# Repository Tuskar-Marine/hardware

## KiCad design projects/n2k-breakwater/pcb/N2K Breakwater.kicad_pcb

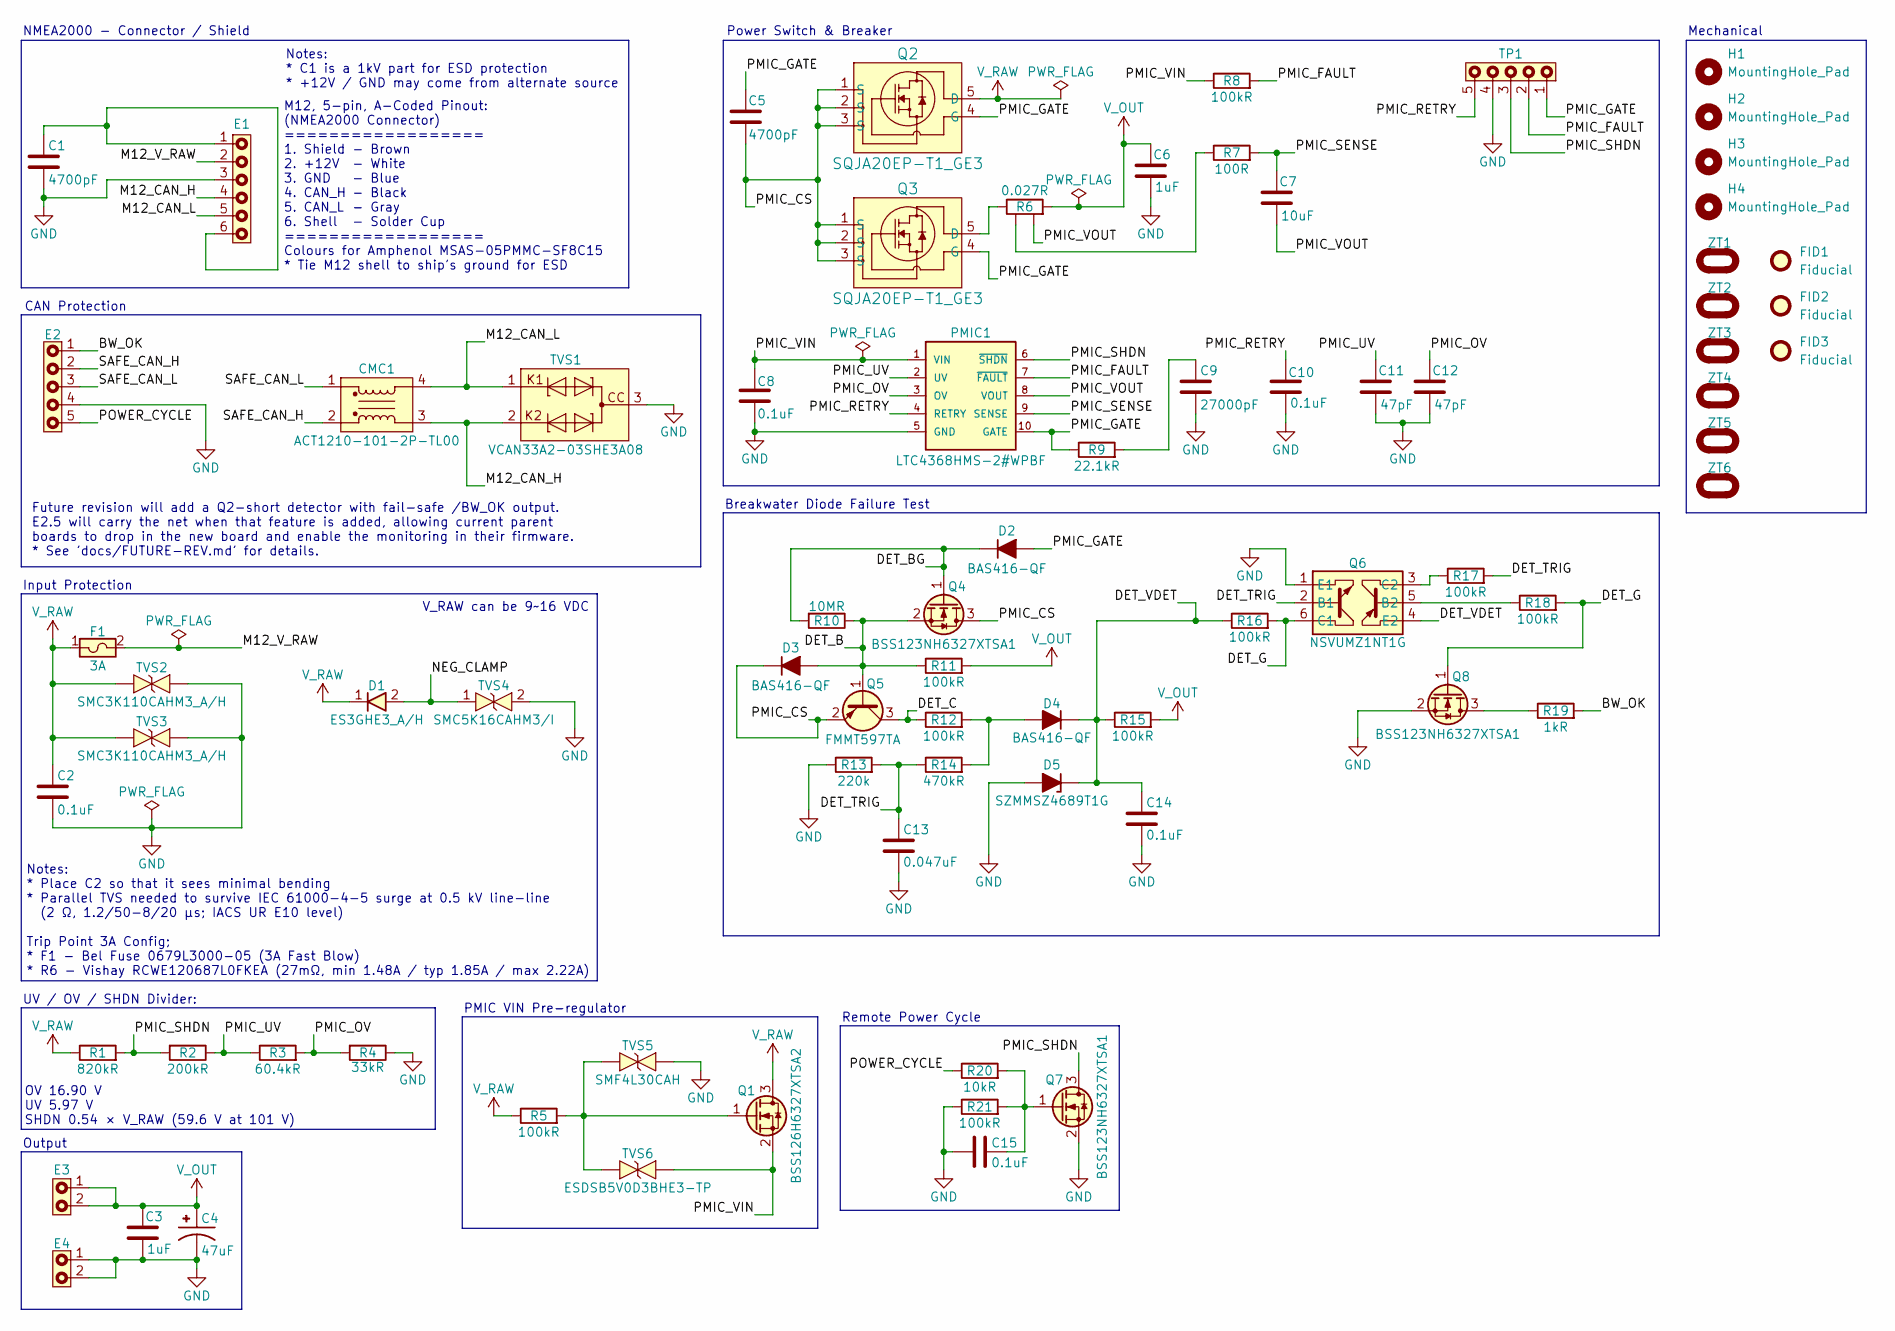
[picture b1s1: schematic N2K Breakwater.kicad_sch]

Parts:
C1, C5: 4700pF; Murata GCJ31BR73A; Part Murata GCJ31BR73A472KXJ1L
C2: 0.1uF; TDK CGA5; Part TDK CGA5L3X7R2E104K160AE
C3, C6: 1uF; Kyocera AVX 0805; Part Kyocera 08051C105K4Z2A
C4: 47uF; Nichicon PCM; Part Nichicon PCM1V470MCL1GS
C7: 10uF; TDK CGA5; Part TDK CGA5L1X7R1H106K160AE
C8, C10, C14, C15: 0.1uF; Kyocera AVX 0805; Part Kyocera 08051C104K4Z2A
C9: 27000pF; Murata GCM0805; Part Murata GCM21B5C2A273JE02K
C11, C12: 47pF; Kemet C0805X; Part Kemet C0805X470J5GACAUTO
C13: 0.047uF; Murata GCJ 0805; Part Murata GCJ21BR72A473KA01L
CMC1: ACT1210-101-2P-TL00; TDK ACT12101012PTL00; Part TDK ACT1210-101-2P-TL00
D1: ES3GHE3_A/H; Vishay ES3G; Part Vishay ES3GHE3_A/H
D2, D3, D4: BAS416-QF; Nexperia BAS416-QF; Part Nexperia BAS416-QF
D5: SZMMSZ4689T1G; Onsemi SZMMSZ4689; Part Onsemi SZMMSZ4689T1G
E1: WireSolderPoint - 1x06 - 2.5mm pitch x 1.0mm diameter; Part n/a
E2: WireSolderPoint - 1x05 - 2.5mm pitch x 1.0mm diameter; Part n/a
E3, E4: WireSolderPoint - 1x02 - 2.5mm pitch x 1.0mm diameter; Part n/a
F1: 3A; Bel Fuse 0679L; Part Bel Fuse 0679L3000-05
FID1, FID2, FID3: Fiducial; Fiducial_1mm_Mask2mm
H1, H2, H3, H4: MountingHole_Pad; MountingHole_5mm_M4_with_Keepout
PMIC1: LTC4368HMS-2#WPBF; ADI LTC4368; Part ADI LTC4368HMS-2#WPBF
Q1: BSS126H6327XTSA2; Infineon BSS126; Part Infineon BSS126H6327XTSA2
Q2, Q3: SQJA20EP-T1_GE3; Vishay SQJA20; Part Vishay SQJA20EP-T1_GE3
Q4, Q7, Q8: BSS123NH6327XTSA1; Infineon BSS123; Part Infineon BSS123NH6327XTSA1
Q5: FMMT597TA; Diodes Inc FMMT597TA; Part Diodes Inc FMMT597TA
Q6: NSVUMZ1NT1G; Onsemi NSVUMZ1; Part Onsemi NSVUMZ1NT1G
R1: 820kR; Panasonic ERA-6K 0805; Part Panasonic ERA-6KEB8203V
R2: 200kR; Stackpole RMCA0603; Part Stackpole RMCA0603FT200K-HP
R3: 60.4kR; Vishay RCA e3 0805; Part Vishay RCA080560K4FKEA
R4: 33kR; Stackpole RMCA0603; Part Stackpole RMCA0603FT33K0-HP
R5, R8, R11, R12, R15, R16, R17, R18, R21: 100kR; Stackpole RMCA0805; Part Stackpole RMCA0805FT100K-HP
R6: 0.027R; Vishay RCWE 1206 4-wire Kelvin; Part Vishay RCWE120627L0FMEA
R7: 100R; Stackpole RMCA0805; Part Stackpole RMCA0805FT100R-HP
R9: 22.1kR; Stackpole RNCP0805; Part Stackpole RNCP0805FTD22K1
R10: 10MR; Stackpole RMCA0603; Part Stackpole RMCA0603FT10M0-HP
R13: 220k; Panasonic ERJ-PC6; Part Panasonic ERJ-PC6D2203V
R14: 470kR; Wurth WRIS-RSKS; Part Wurth 560112120009
R19: 1kR; Stackpole RNCP0805; Part Stackpole RNCP0805FTD1K00
R20: 10kR; Stackpole RNCP0805; Part Stackpole RNCP0805FTD10K0
TP1: WireSolderPoint - 1x05 - 2.5mm pitch x 1.0mm diameter; Part n/a
TVS1: VCAN33A2-03SHE3A08; Vishay VCAN33A2-03S; Part Vishay VCAN33A2-03SHE3A08
TVS2, TVS3: SMC3K110CAHM3_A/H; Vishay SMC3K110; Part Vishay SMC3K110CAHM3_A/H
TVS4: SMC5K16CAHM3/I; Vishay SMC5K16CA; Part Vishay SMC5K16CAHM3/I
TVS5: SMF4L30CAH; TSC SMF4L30CAH; Part TSC SMF4L30CAH
TVS6: ESDSB5V0D3BHE3-TP; MCC ESDSB5V0D3; Part MCC ESDSB5V0D3BHE3-TP
ZT1, ZT2, ZT3, ZT4, ZT5, ZT6: Tuskar Ziptie Slot 4.5x2mm

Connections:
/BW_OK: E2.1, R19.2
/DET_B: D3.2 (A), Q4.2 (S), Q5.1 (B), R10.2, R11.1
/DET_BG: D2.1 (K), Q4.1 (G), R10.1
/DET_C: Q5.3 (C), R12.1
/DET_G: Q6.6 (C1), Q8.1 (G), R16.2, R18.2
/DET_TRIG: C13.1, Q6.2 (B1), R13.2, R14.1, R17.2
/DET_VDET: C14.1, D4.1 (K), D5.1 (K), Q6.4 (E2), R15.1, R16.1
/M12_CAN_H: CMC1.3 (O2), E1.4, TVS1.2
/M12_CAN_L: CMC1.4 (O1), E1.5, TVS1.1
/M12_V_RAW: E1.2, F1.2
/NEG_CLAMP: D1.2 (A), TVS4.1
/PMIC_CS: C5.1, D3.1 (K), Q2.1 (S), Q2.2 (S), Q2.3 (S), Q3.1 (S), Q3.2 (S), Q3.3 (S), Q4.3 (D), Q5.2 (E)
/PMIC_FAULT: PMIC1.7 (~FAULT), R8.2, TP1.2
/PMIC_GATE: C5.2, D2.2 (A), PMIC1.10 (GATE), Q2.4 (G), Q3.4 (G), R9.1, TP1.1
/PMIC_OV: C12.1, PMIC1.3 (OV), R3.2, R4.1
/PMIC_RETRY: C10.2, PMIC1.4 (RETRY), TP1.5
/PMIC_SENSE: C7.2, PMIC1.9 (SENSE), R7.2
/PMIC_SHDN: PMIC1.6 (~SHDN), Q7.3 (D), R1.2, R2.1, TP1.3
/PMIC_UV: C11.1, PMIC1.2 (UV), R2.2, R3.1
/PMIC_VIN: C8.1, PMIC1.1 (VIN), Q1.2 (S), R8.1, TVS6.2
/PMIC_VOUT: C7.1, PMIC1.8 (VOUT), R6.3
/POWER_CYCLE: E2.5, R20.1
/SAFE_CAN_H: CMC1.2 (I2), E2.2
/SAFE_CAN_L: CMC1.1 (I1), E2.3
GND: C1.1, C2.2, C3.2, C4.2, C6.2, C8.2, C9.2, C10.1, C11.2, C12.2, C13.2, C14.2, C15.1, D5.2 (A), E1.3, E2.4, E4.1, E4.2, PMIC1.5 (GND), Q6.1 (E1), Q7.2 (S), Q8.2 (S), R4.2, R13.1, R21.1, TP1.4, TVS1.3, TVS2.2, TVS3.2, TVS4.2, TVS5.2
unnamed: C1.2, E1.1, E1.6
unnamed: C9.1, R9.2
unnamed: D4.2 (A), R12.2, R14.2
unnamed: Q1.1 (G), R5.2, TVS5.1, TVS6.1
unnamed: Q3.5 (D), R6.2
unnamed: Q6.5 (B2), R18.1
unnamed: Q6.3 (C2), R17.1
unnamed: C15.2, Q7.1 (G), R20.2, R21.2
unnamed: Q8.3 (D), R19.1
unnamed: R6.4, R7.1
V_OUT: C3.1, C4.1, C6.1, E3.1, E3.2, R6.1, R11.2, R15.2
V_RAW: C2.1, D1.1 (K), F1.1, Q1.3 (D), Q2.5 (D), R1.1, R5.1, TVS2.1, TVS3.1

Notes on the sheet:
Remote Power Cycle
CAN Protection
V_RAW can be 9~16 VDC
PMIC VIN Pre-regulator
Output
Notes: * C1 is a 1kV part for ESD protection * +12V / GND may come from alternate source
M12, 5-pin, A-Coded Pinout: (NMEA2000 Connector) ================== 1. Shield 2. +12V 3. GND 4. CAN_H 5. CAN_L 6. Shell ================== Colours for Amphenol MSAS-05PMMC-SF8C15 * Tie M12 shell to ship's ground for ESD
Future revision will add a Q2-short detector with fail-safe /BW_OK output. E2.5 will carry the net when that feature is added, allowing current parent boards to drop in the new board and enable the monitoring in their firmware. * See 'docs/FUTURE-REV.md' for details.
Input Protection
Power Switch & Breaker
UV / OV / SHDN Divider:
Notes: * Place C2 so that it sees minimal bending * Parallel TVS needed to survive IEC 61000-4-5 surge at 0.5 kV line-line (2 Ω, 1.2/50-8/20 µs; IACS UR E10 level) Trip Point 3A Config; * F1 - Bel Fuse 0679L3000-05 (3A Fast Blow) * R6 - Vishay RCWE120687L0FKEA (27mΩ, min 1.48A / typ 1.85A / max 2.2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
NMEA2000 - Connector / Shield
Breakwater Diode Failure Test
Mechanical
OV 16.90 V UV 5.97 V SHDN 0.54 × V_RAW (59.6 V at 101 V)
- Brown - White - Blue - Black - Gray - Solder Cup

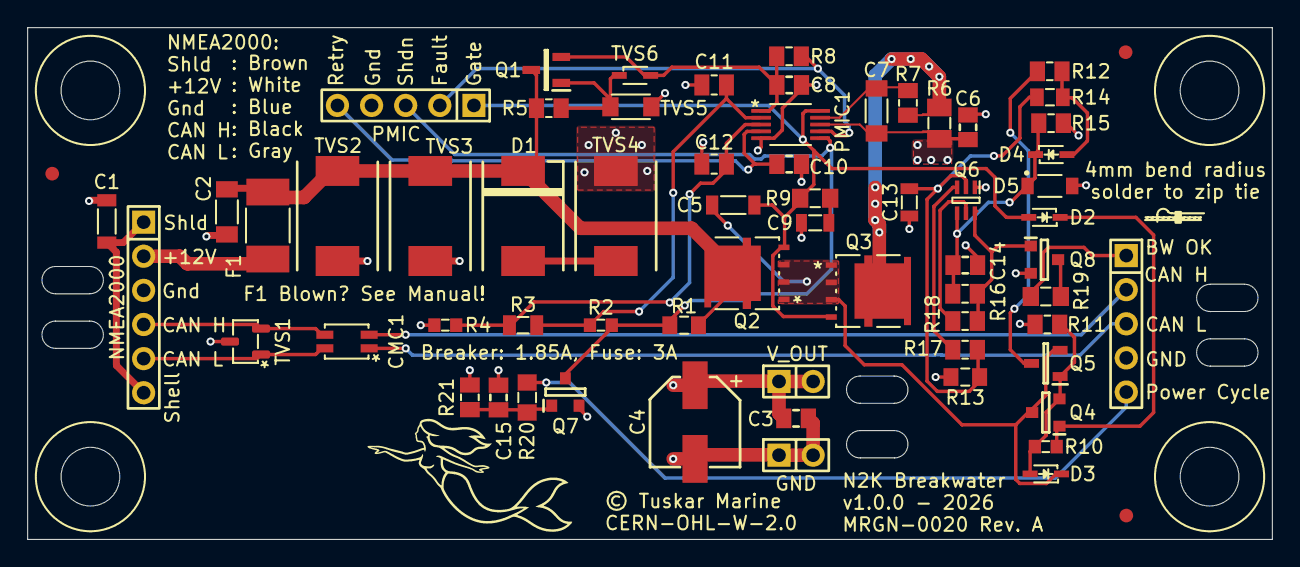
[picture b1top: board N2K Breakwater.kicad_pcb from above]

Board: 4 copper layers, 91.2 x 37.5 mm, 76 parts (0 on the bottom side), 37 nets.

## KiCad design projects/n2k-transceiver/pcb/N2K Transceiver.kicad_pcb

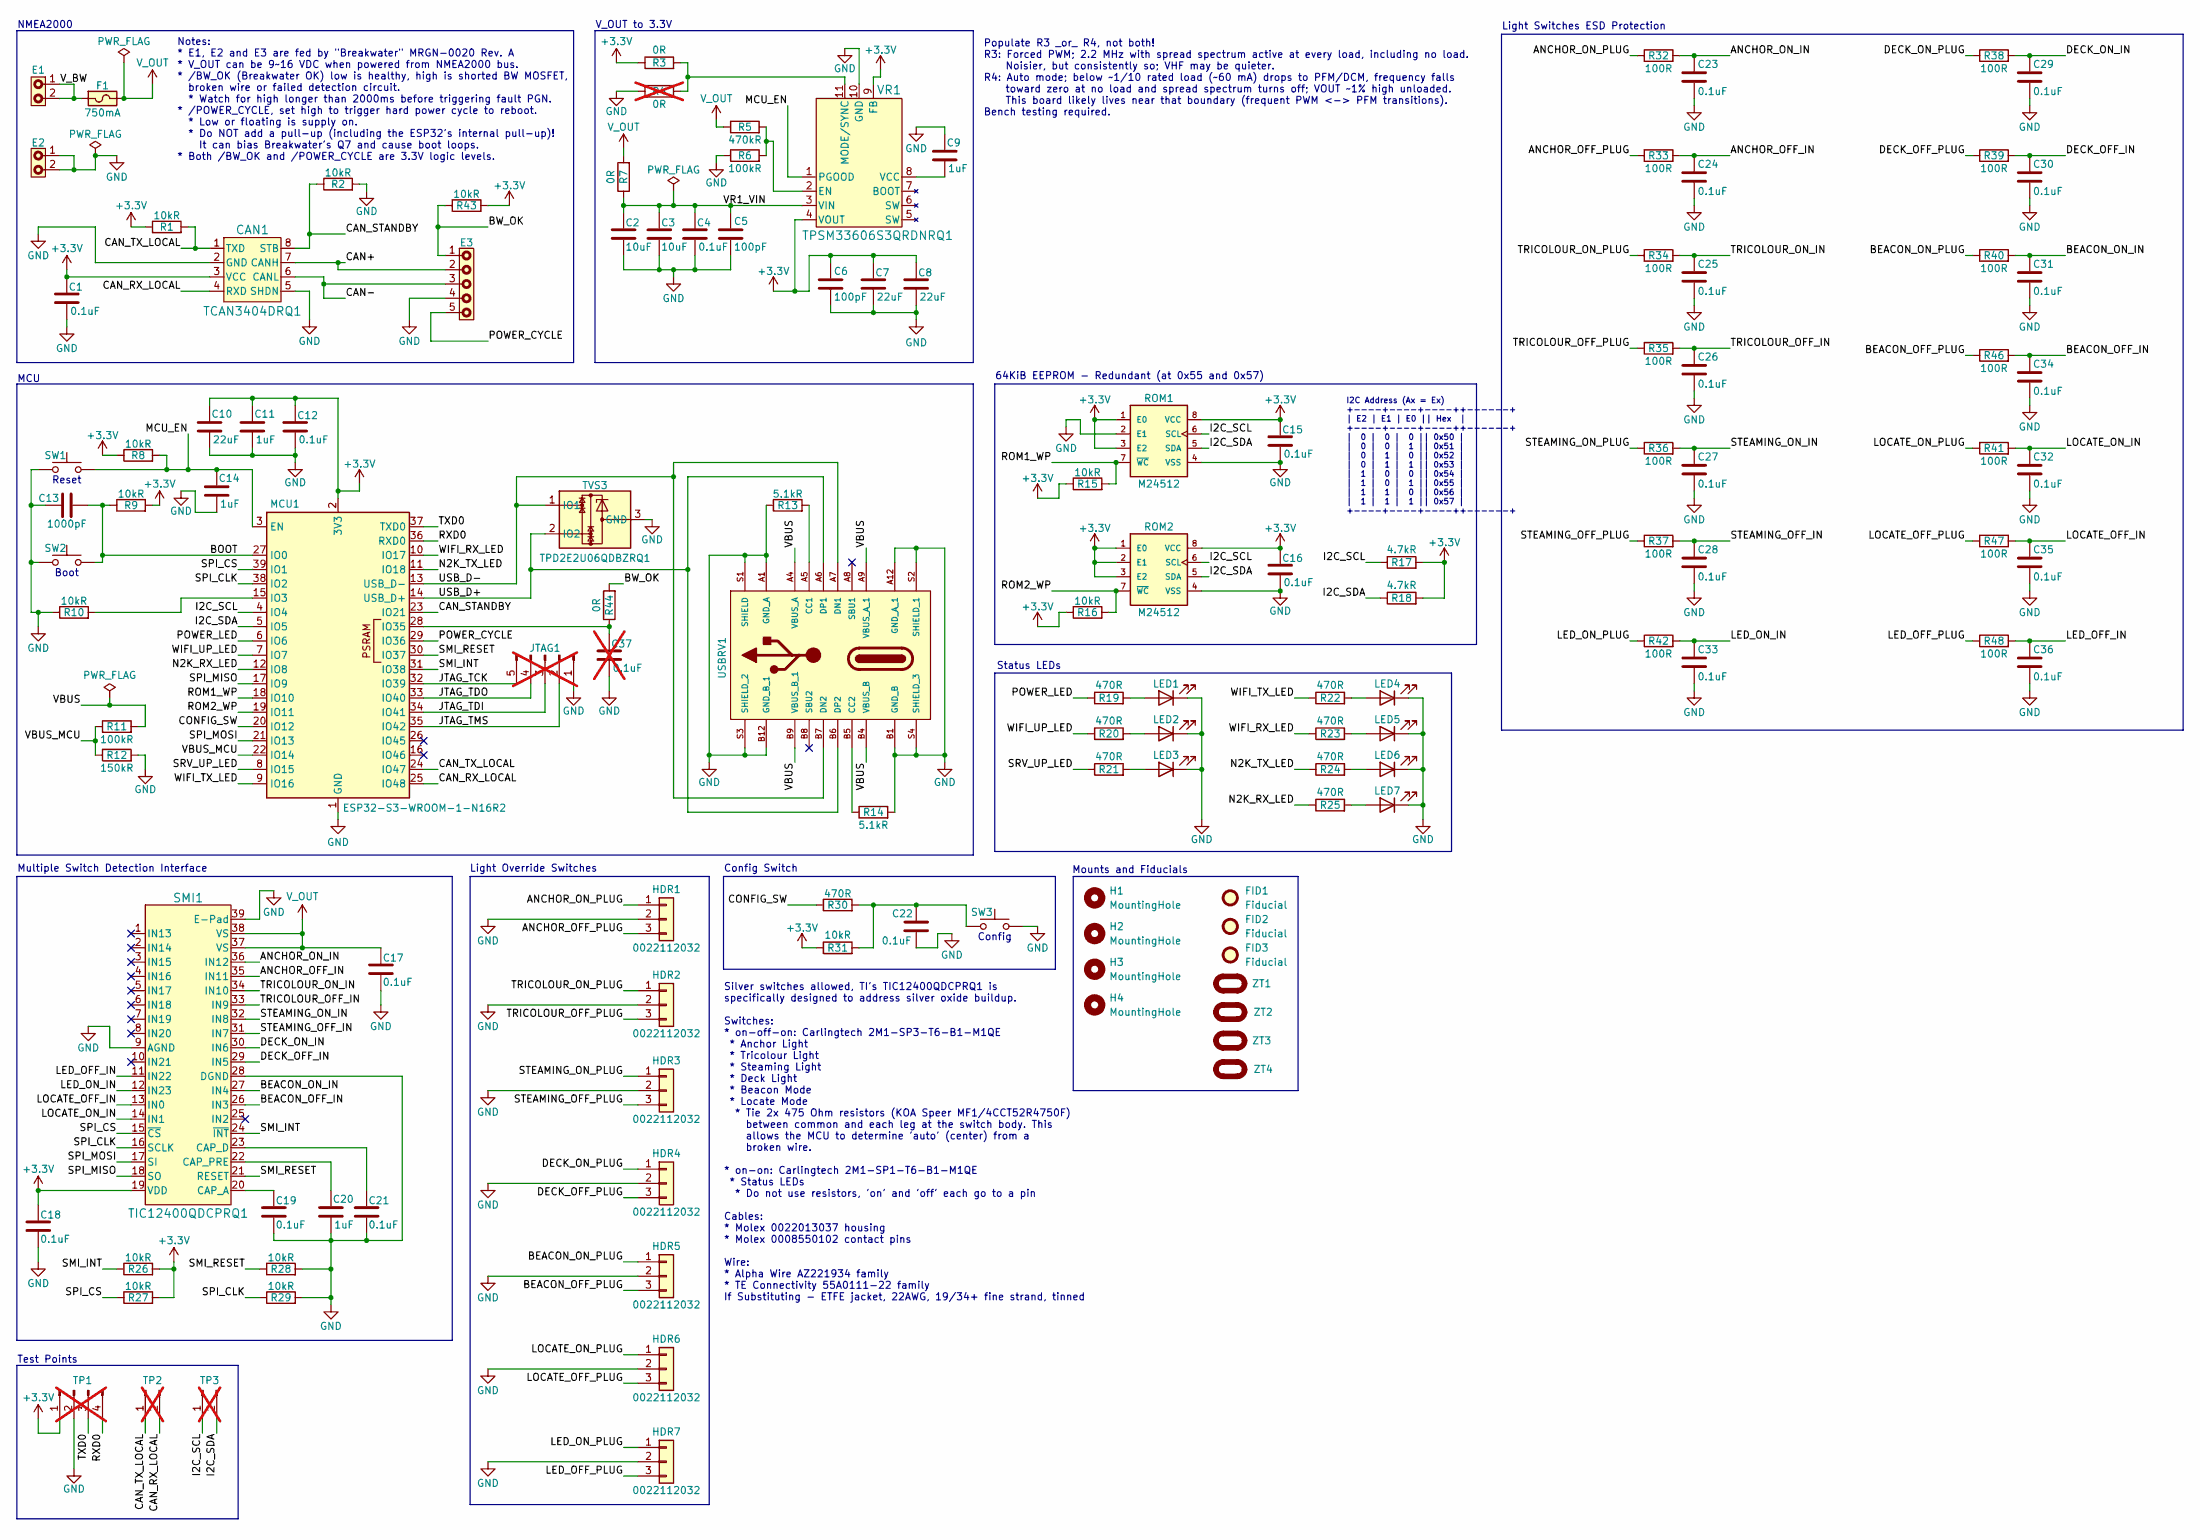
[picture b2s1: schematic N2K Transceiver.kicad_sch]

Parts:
C1, C4, C12, C15, C16, C17, C18, C19, C21, C22, C23, C24, C25, C26, C27, C28, C29, C30, C31, C32, C33, C34, C35, C36: 0.1uF; Kyocera AVX 0805; Part Kyocera 08051C104K4Z2A
C2, C3: 10uF; TDK CGA5; Part TDK CGA5L1X7R1H106K160AE
C5, C6: 100pF; Kemet C0805X; Part Kemet C0805X101J5GACAUTO
C7, C8, C10: 22uF; Murata GCJ32ER71C; Part Murata GCJ32ER71C226KE01L
C9, C11, C14, C20: 1uF; Kyocera AVX 0805; Part Kyocera 08051C105K4Z2A
C13: 1000pF; TDK CGA 0805; Part TDK CGA4F2X7R2A102K085AE
C37: 0.1uF; Kyocera AVX 0805; Part Kyocera 08051C104K4Z2A; not fitted
CAN1: TCAN3404DRQ1; TI TCAN3404; Part TI TCAN3404DRQ1
E1, E2: WireSolderPoint - 1x02 - 2.5mm pitch x 1.0mm diameter; Part n/a
E3: WireSolderPoint - 1x05 - 2.5mm pitch x 1.0mm diameter; Part n/a
F1: 750mA; Bel Fuse 0679L; Part Bel Fuse 0679L0750-05
FID1, FID2, FID3: Fiducial; Fiducial_1mm_Mask2mm
H1, H2, H3, H4: MountingHole; MountingHole_5mm_M4_with_Keepout
HDR1, HDR2, HDR3, HDR4, HDR5, HDR6, HDR7: 0022112032; Molex 0022112032; Part Molex 0022112032
JTAG1: Conn_01x05_Pin; PinHeader_1x05_P1.27mm_Vertical; not fitted
LED1, LED2, LED3, LED4, LED5, LED6, LED7: TLMS1101-GS15; Vishay TLMS1101; Part Vishay TLMS1101-GS15
MCU1: ESP32-S3-WROOM-1-N16R2; Espressif ESP32-S3; Part Espressif ESP32-S3-WROOM-1-N16R2
R1, R2, R8, R9, R10, R15, R16, R26, R27, R28, R29, R31, R43: 10kR; Stackpole RMCA0805; Part Stackpole RMCA0805FT10K0-HP
R3, R7, R44: 0R; Vishay RCA-SR e3 0805; Part Vishay RCA08050000ZSEASR
R4: 0R; Vishay RCA-SR e3 0805; Part Vishay RCA08050000ZSEASR; not fitted
R5: 470kR; Wurth WRIS-RSKS; Part Wurth 560112120009
R6, R11: 100kR; Stackpole RMCA0805; Part Stackpole RMCA0805FT100K-HP
R12: 150kR; Vishay RCA e3 0805; Part Vishay RCA0805150KFKEA
R13, R14: 5.1kR; Vishay RCA e3 0805; Part Vishay RCA08055K10FKEA
R17, R18: 4.7kR; Stackpole RMCA0805; Part Stackpole RMCA0805FT4K70-HP
R19, R20, R21, R22, R23, R24, R25, R30: 470R; Stackpole RMCA0805; Part Stackpole RMCA0805FT470R-HP
R32, R33, R34, R35, R36, R37, R38, R39, R40, R41, R42, R46, R47, R48: 100R; Stackpole RMCA0805; Part Stackpole RMCA0805FT100R-HP
ROM1, ROM2: M24512; STM M24512; Part STM M24512-DRMN8TP/K
SMI1: TIC12400QDCPRQ1; TI TIC12400QDCPRQ1; Part TI TIC12400QDCPRQ1
SW1, SW2, SW3: TS03-66-50-BK-160-LCR-D-67; Same Sky TS03-66; Part Same Sky TS03-66-50-BK-160-LCR-D-67
TP1: Power/UART Test Point; PinHeader_1x04_P2.54mm_Vertical; not fitted
TP2: Logic CAN Test Point; PinHeader_1x02_P1.27mm_Vertical; not fitted
TP3: I2C Test Point; PinHeader_1x02_P1.27mm_Vertical; not fitted
TVS3: TPD2E2U06QDBZRQ1; TI TPD2E2U06; Part TI TPD2E2U06QDBZRQ1
USBRV1: USB4145-03-0170-C; GCT USB4145-03-0170-C; Part GCT USB4145-03-0170-C
VR1: TPSM33606S3QRDNRQ1; TI TPSM336; Part TI TPSM33606S3QRDNRQ1
ZT1, ZT2, ZT3, ZT4: Tuskar Ziptie Slot 4.5x2mm

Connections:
+3.3V: C1.1, C6.1, C7.1, C8.1, C10.1, C11.1, C12.1, C15.1, C16.1, C18.1, CAN1.3 (VCC), MCU1.2 (3V3), R1.1, R3.1, R8.1, R9.2, R15.1, R16.1, R17.2, R18.2, R26.2, R27.2, R31.1, R43.2, ROM1.1 (E0), ROM1.3 (E2), ROM1.8 (VCC), ROM2.1 (E0), ROM2.2 (E1), ROM2.3 (E2), ROM2.8 (VCC), SMI1.19 (VDD), TP1.1, VR1.4 (VOUT), VR1.9 (FB)
/ANCHOR_OFF_IN: C24.1, R33.2, SMI1.35 (IN11)
/ANCHOR_OFF_PLUG: HDR1.3, R33.1
/ANCHOR_ON_IN: C23.1, R32.2, SMI1.36 (IN12)
/ANCHOR_ON_PLUG: HDR1.1, R32.1
/BEACON_OFF_IN: C34.1, R46.2, SMI1.26 (IN3)
/BEACON_OFF_PLUG: HDR5.3, R46.1
/BEACON_ON_IN: C31.1, R40.2, SMI1.27 (IN4)
/BEACON_ON_PLUG: HDR5.1, R40.1
/BOOT: C13.2, MCU1.27 (IO0), R9.1, SW2.1 (A), SW2.2 (A)
/BW_OK: E3.1, R43.1, R44.2
/CAN+: CAN1.7 (CANH), E3.2
/CAN-: CAN1.6 (CANL), E3.3
/CAN_RX_LOCAL: CAN1.4 (RXD), MCU1.25 (IO48), TP2.2
/CAN_STANDBY: CAN1.8 (STB), MCU1.23 (IO21), R2.1
/CAN_TX_LOCAL: CAN1.1 (TXD), MCU1.24 (IO47), R1.2, TP2.1
/CONFIG_SW: MCU1.20 (IO12), R30.1
/DECK_OFF_IN: C30.1, R39.2, SMI1.29 (IN5)
/DECK_OFF_PLUG: HDR4.3, R39.1
/DECK_ON_IN: C29.1, R38.2, SMI1.30 (IN6)
/DECK_ON_PLUG: HDR4.1, R38.1
/I2C_SCL: MCU1.4 (IO4), R17.1, ROM1.6 (SCL), ROM2.6 (SCL), TP3.1
/I2C_SDA: MCU1.5 (IO5), R18.1, ROM1.5 (SDA), ROM2.5 (SDA), TP3.2
/JTAG_TCK: JTAG1.5, MCU1.32 (IO39)
/JTAG_TDI: JTAG1.3, MCU1.34 (IO41)
/JTAG_TDO: JTAG1.4, MCU1.33 (IO40)
/JTAG_TMS: JTAG1.2, MCU1.35 (IO42)
/LED_OFF_IN: C36.1, R48.2, SMI1.11 (IN22)
/LED_OFF_PLUG: HDR7.3, R48.1
/LED_ON_IN: C33.1, R42.2, SMI1.12 (IN23)
/LED_ON_PLUG: HDR7.1, R42.1
/LOCATE_OFF_IN: C35.1, R47.2, SMI1.13 (IN0)
/LOCATE_OFF_PLUG: HDR6.3, R47.1
/LOCATE_ON_IN: C32.1, R41.2, SMI1.14 (IN1)
/LOCATE_ON_PLUG: HDR6.1, R41.1
/MCU_EN: C14.1, MCU1.3 (EN), R8.2, SW1.1 (A), SW1.2 (A), VR1.1 (PGOOD)
/N2K_RX_LED: MCU1.12 (IO8), R25.1
/N2K_TX_LED: MCU1.11 (IO18), R24.1
/POWER_CYCLE: E3.5, MCU1.29 (IO36)
/POWER_LED: MCU1.6 (IO6), R19.1
/ROM1_WP: MCU1.18 (IO10), R15.2, ROM1.7 (~WC)
/ROM2_WP: MCU1.19 (IO11), R16.2, ROM2.7 (~WC)
/RXD0: MCU1.36 (RXD0), TP1.4
/SMI_INT: MCU1.31 (IO38), R26.1, SMI1.24 (~INT)
/SMI_RESET: MCU1.30 (IO37), R28.1, SMI1.21 (RESET)
/SPI_CLK: MCU1.38 (IO2), R29.1, SMI1.16 (SCLK)
/SPI_CS: MCU1.39 (IO1), R27.1, SMI1.15 (~CS)
/SPI_MISO: MCU1.17 (IO9), SMI1.18 (SO)
/SPI_MOSI: MCU1.21 (IO13), SMI1.17 (SI)
/SRV_UP_LED: MCU1.8 (IO15), R21.1
/STEAMING_OFF_IN: C28.1, R37.2, SMI1.31 (IN7)
/STEAMING_OFF_PLUG: HDR3.3, R37.1
/STEAMING_ON_IN: C27.1, R36.2, SMI1.32 (IN8)
/STEAMING_ON_PLUG: HDR3.1, R36.1
/TRICOLOUR_OFF_IN: C26.1, R35.2, SMI1.33 (IN9)
/TRICOLOUR_OFF_PLUG: HDR2.3, R35.1
/TRICOLOUR_ON_IN: C25.1, R34.2, SMI1.34 (IN10)
/TRICOLOUR_ON_PLUG: HDR2.1, R34.1
/TXD0: MCU1.37 (TXD0), TP1.3
/USB_D+: MCU1.14 (USB_D+), TVS3.2 (IO2), USBRV1.A6 (DP1), USBRV1.B6 (DP2)
/USB_D-: MCU1.13 (USB_D-), TVS3.1 (IO1), USBRV1.A7 (DN1), USBRV1.B7 (DN2)
/VBUS: R11.2, USBRV1.A4 (VBUS_A), USBRV1.A9 (VBUS_A_1), USBRV1.B4 (VBUS_B), USBRV1.B9 (VBUS_B_1)
/VBUS_MCU: MCU1.22 (IO14), R11.1, R12.1
/VR1_VIN: C2.1, C3.1, C4.1, C5.1, R7.1, VR1.3 (VIN)
/V_BW: E1.1, E1.2, F1.1
/WIFI_RX_LED: MCU1.10 (IO17), R23.1
/WIFI_TX_LED: MCU1.9 (IO16), R22.1
/WIFI_UP_LED: MCU1.7 (IO7), R20.1
GND: C1.2, C2.2, C3.2, C4.2, C5.2, C6.2, C7.2, C8.2, C9.1, C10.2, C11.2, C12.2, C13.1, C14.2, C15.2, C16.2, C17.2, C18.2, C19.2, C20.2, C21.2, C22.1, C23.2, C24.2, C25.2, C26.2, C27.2, C28.2, C29.2, C30.2, C31.2, C32.2, C33.2, C34.2, C35.2, C36.2, C37.2, CAN1.2 (GND), CAN1.5 (SHDN), E2.1, E2.2, E3.4, HDR1.2, HDR2.2, HDR3.2, HDR4.2, HDR5.2, HDR6.2, HDR7.2, JTAG1.1, LED1.1 (K), LED2.1 (K), LED3.1 (K), LED4.1 (K), LED5.1 (K), LED6.1 (K), LED7.1 (K), MCU1.1 (GND), MCU1.40 (GND), MCU1.41 (GND), R2.2, R4.2, R6.1, R10.1, R12.2, R13.1, R14.2, R28.2, R29.2, ROM1.2 (E1), ROM1.4 (VSS), ROM2.4 (VSS), SMI1.9 (AGND), SMI1.28 (DGND), SMI1.39 (E-Pad), SW1.3 (B), SW1.4 (B), SW2.3 (B), SW2.4 (B), SW3.3 (B), SW3.4 (B), TP1.2, TVS3.3 (GND), USBRV1.A1 (GND_A), USBRV1.A12 (GND_A_1), USBRV1.B1 (GND_B), USBRV1.B12 (GND_B_1), USBRV1.S1 (SHIELD), USBRV1.S2 (SHIELD_1), USBRV1.S3 (SHIELD_2), USBRV1.S4 (SHIELD_3), VR1.10 (GND)
unnamed: C22.2, R30.2, R31.2, SW3.1 (A), SW3.2 (A)
unnamed: LED1.2 (A), R19.2
unnamed: LED2.2 (A), R20.2
unnamed: LED3.2 (A), R21.2
unnamed: LED4.2 (A), R22.2
unnamed: LED5.2 (A), R23.2
unnamed: LED6.2 (A), R24.2
unnamed: LED7.2 (A), R25.2
unnamed: MCU1.15 (IO3), R10.2
unnamed: C37.1, MCU1.28 (IO35), R44.1
unnamed: C19.1, SMI1.20 (CAP_A)
unnamed: C21.1, SMI1.23 (CAP_D)
unnamed: C20.1, SMI1.22 (CAP_PRE)
unnamed: R13.2, USBRV1.A5 (CC1)
unnamed: R14.1, USBRV1.B5 (CC2)
unnamed: R5.2, R6.2, VR1.2 (EN)
unnamed: R3.2, R4.1, VR1.11 (MODE/SYNC)
unnamed: C9.2, VR1.8 (VCC)
V_OUT: C17.1, F1.2, R5.1, R7.2, SMI1.37 (VS), SMI1.38 (VS)

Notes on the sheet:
Notes: * E1, E2 and E3 are fed by "Breakwater" MRGN-0020 Rev. A * V_OUT can be 9~16 VDC when powered from NMEA2000 bus. * /BW_OK (Breakwater OK) low is healthy, high is shorted BW MOSFET, broken wire or failed detection circuit. * Watch for high longer than 2000ms before triggering fault PGN. * /PO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
Config Switch
MCU
Silver switches allowed, TI's TIC12400QDCPRQ1 is specifically designed to address silver oxide buildup. Switches: * on-off-on: Carlingtech 2M1-SP3-T6-B1-M1QE * Anchor Light * Tricolour Light * Steaming Light * Deck Light * Beacon Mode * Locate Mode * Tie 2x 475 Ohm resistors (KOA Speer MF1/4CCT52R4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
Multiple Switch Detection Interface
Mounts and Fiducials
Test Points
Boot
Light Override Switches
Status LEDs
NMEA2000
I2C Address (Ax = Ex) +----+----+----++------+ | E2 | E1 | E0 || Hex | +----+----+----++------+ | 0 | 0 | 0 || 0x50 | | 0 | 0 | 1 || 0x51 | | 0 | 1 | 0 || 0x52 | | 0 | 1 | 1 || 0x53 | | 1 | 0 | 0 || 0x54 | | 1 | 0 | 1 || 0x55 | | 1 | 1 | 0 || 0x56 | | 1 | 1 | 1 || 0x57 | +----+----+----++------+
Config
Reset
Populate R3 _or_ R4, not both! R3: Forced PWM; 2.2 MHz with spread spectrum active at every load, including no load. Noisier, but consistently so; VHF may be quieter. R4: Auto mode; below ~1/10 rated load (~60 mA) drops to PFM/DCM, frequency falls toward zero at no load and spread spectrum turns of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
V_OUT to 3.3V
Light Switches ESD Protection
64KiB EEPROM - Redundant (at 0x55 and 0x57)

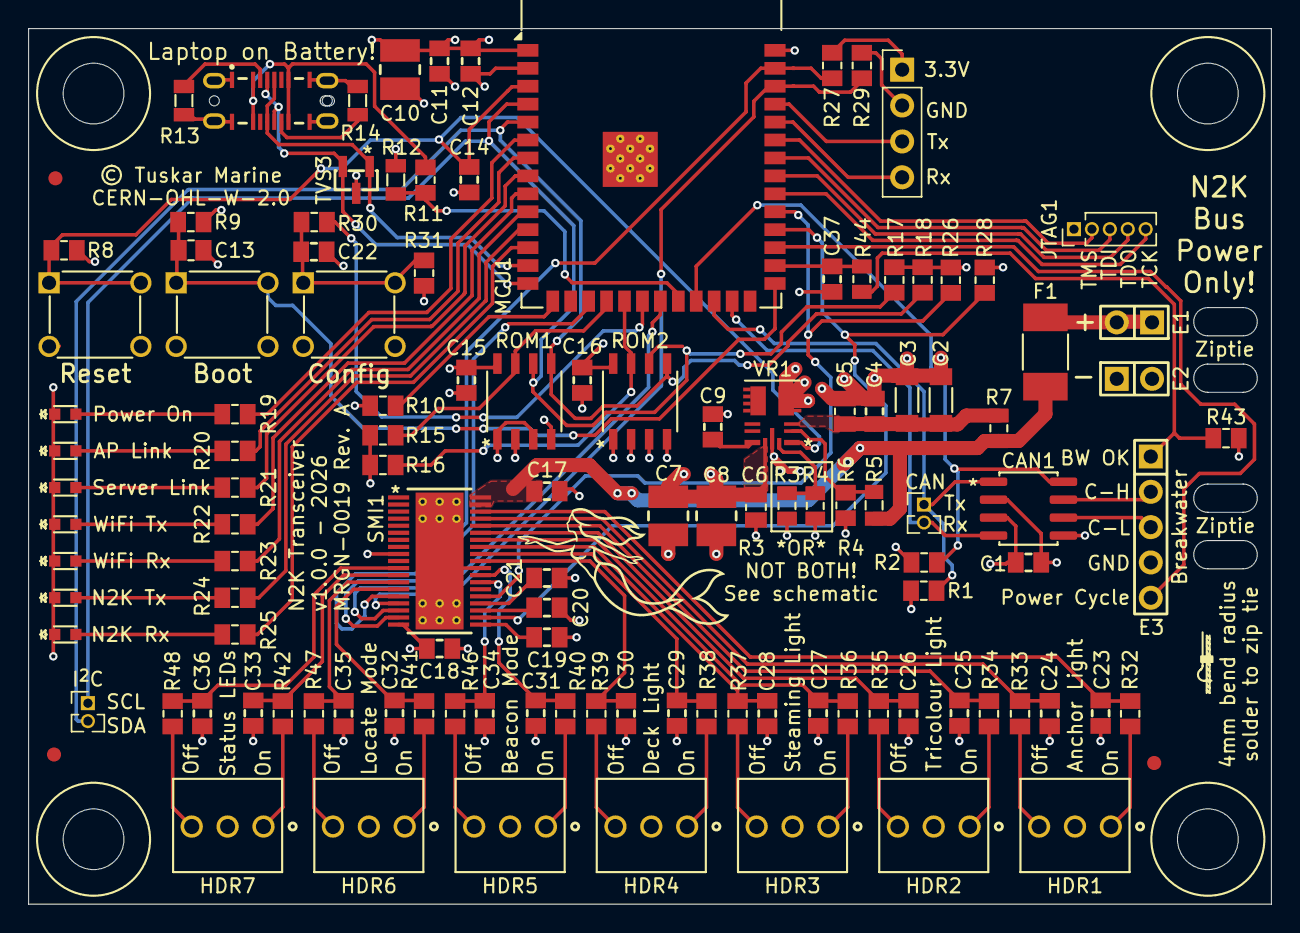
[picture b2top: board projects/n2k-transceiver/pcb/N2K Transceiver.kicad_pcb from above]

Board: 4 copper layers, 88.0 x 62.0 mm, 128 parts (0 on the bottom side), 88 nets.

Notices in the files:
projects/n2k-breakwater/pcb/N2K Breakwater.kicad_pcb:
© Tuskar Marine
CERN-OHL-W-2.0
